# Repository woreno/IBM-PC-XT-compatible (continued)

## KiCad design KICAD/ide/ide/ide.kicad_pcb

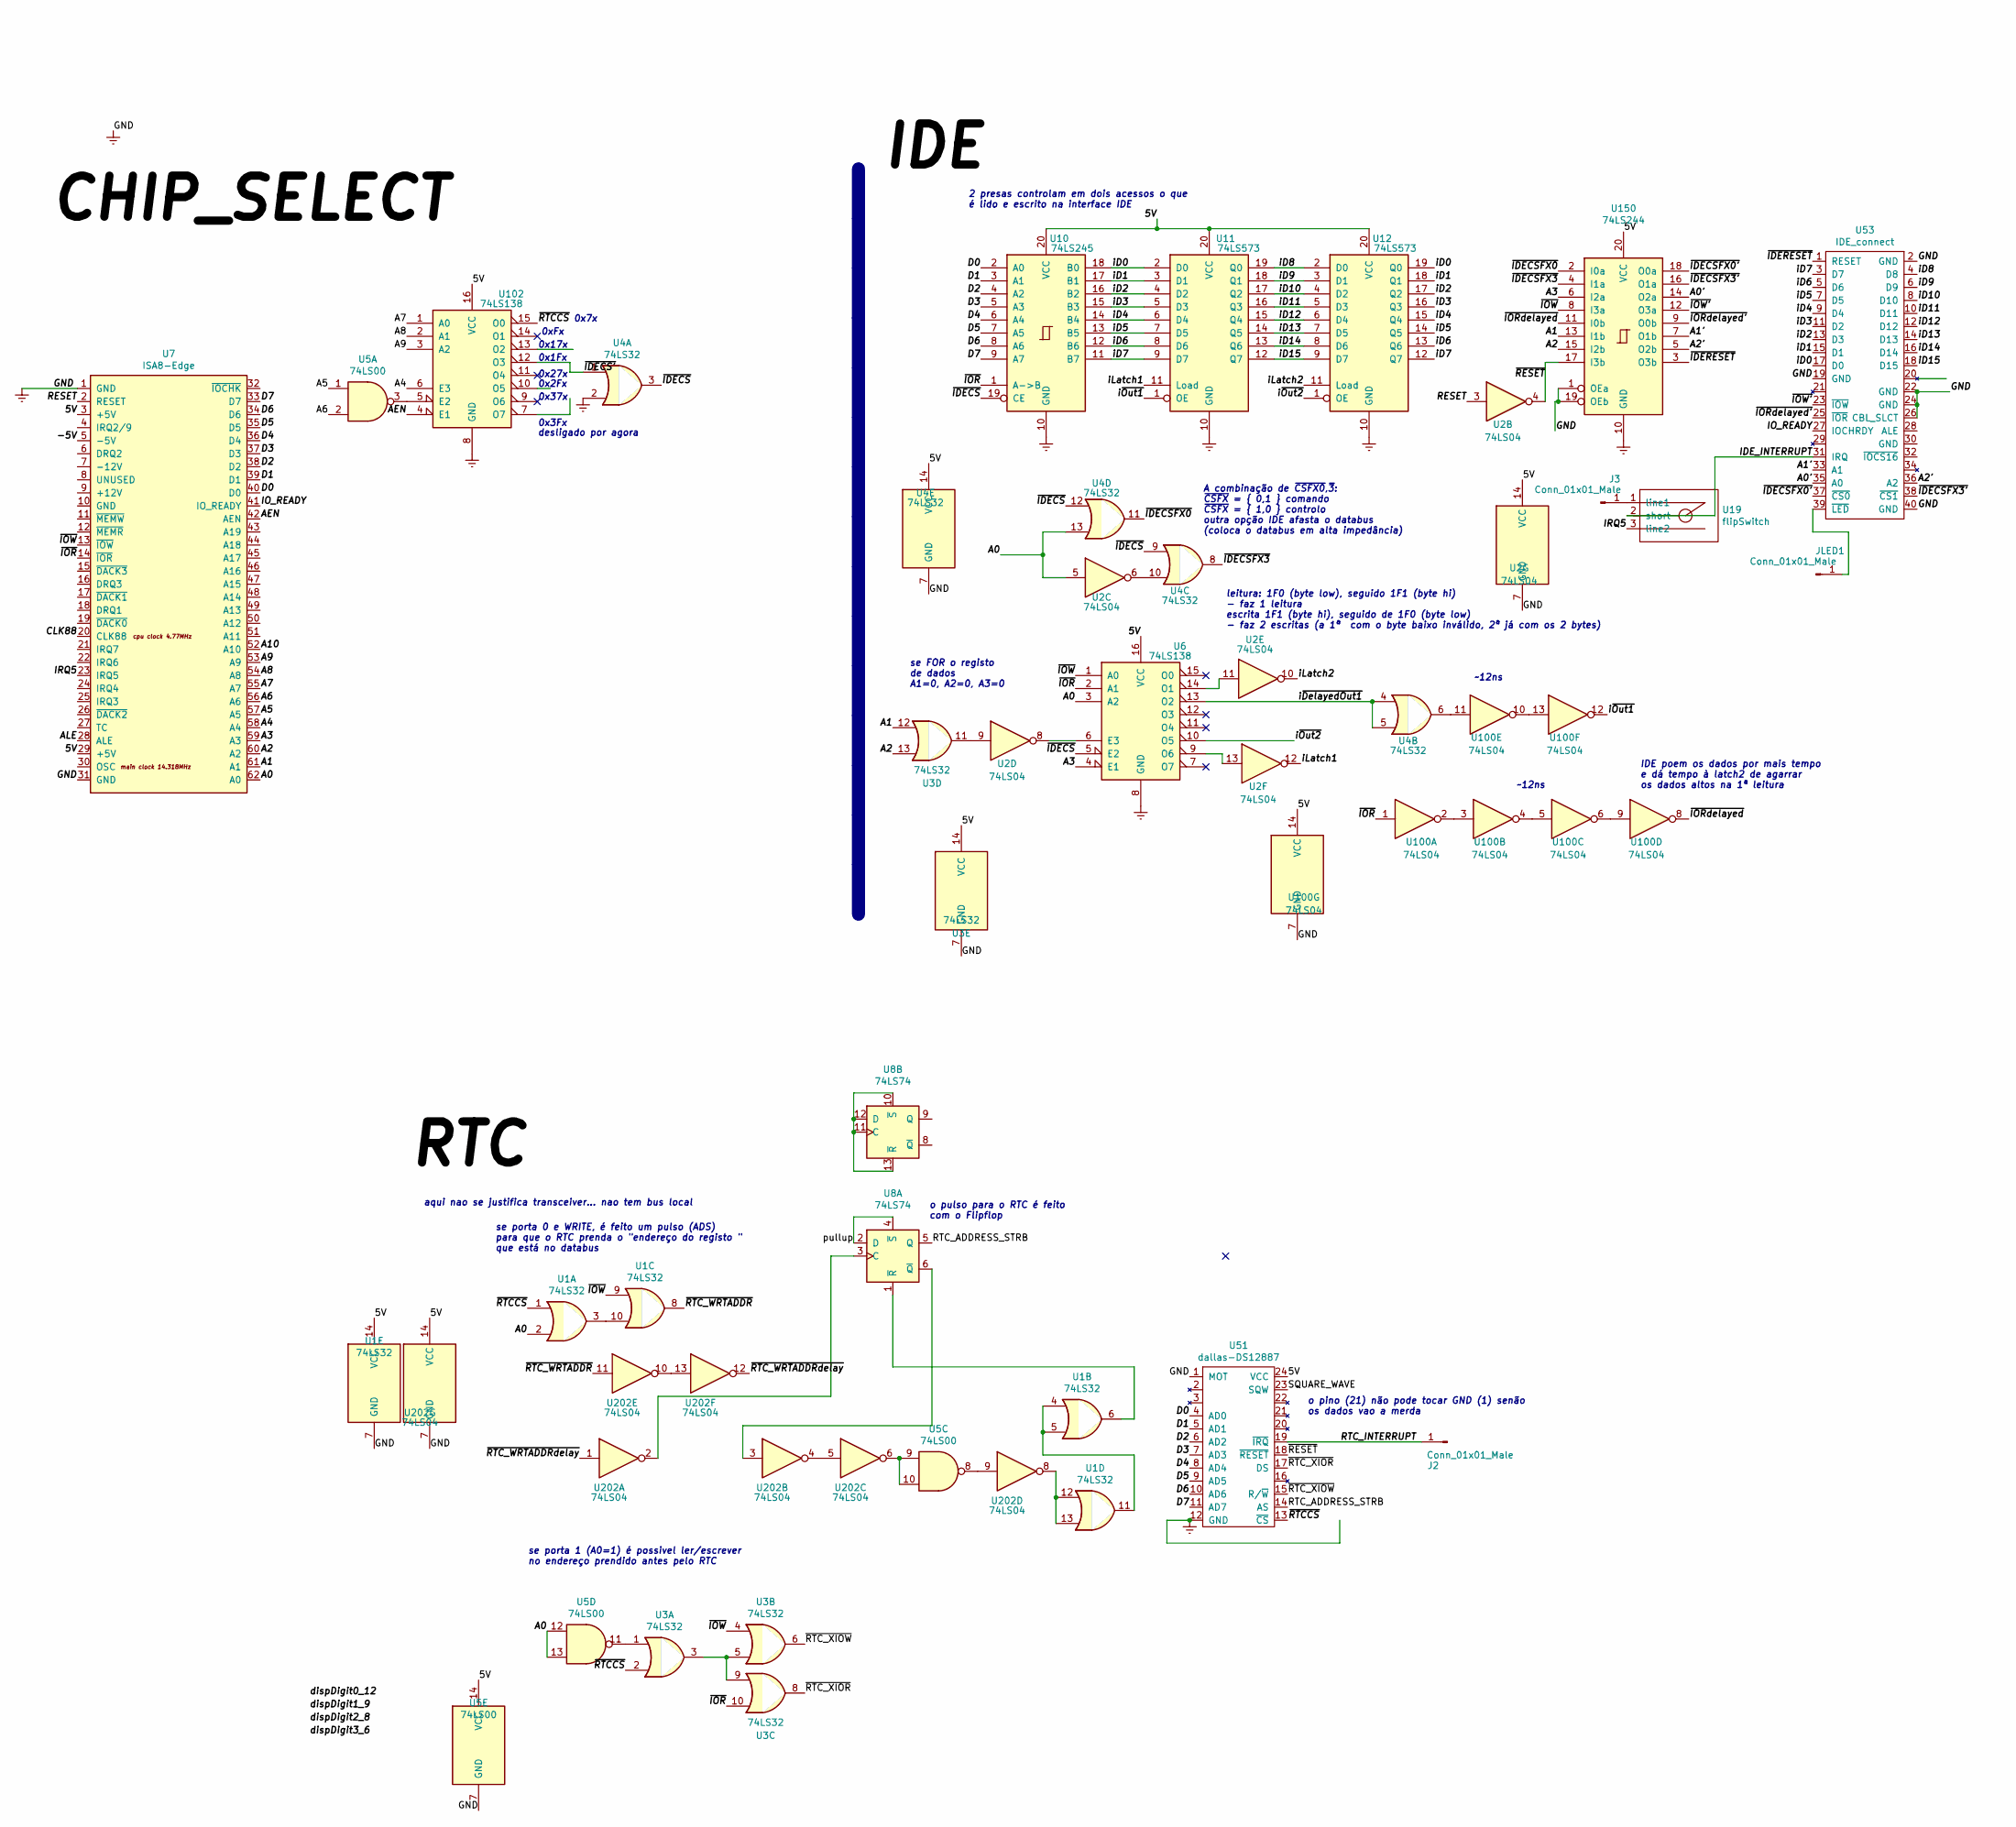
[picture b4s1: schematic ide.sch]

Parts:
J2, J3: Conn_01x01_Male; Conector1x1_Oval
JLED1: Conn_01x01_Male; Conector1x1_Oval
U1, U3, U4: 74LS32; standard_DIP_14OvalPins
U2, U100, U202: 74LS04; standard_DIP_14OvalPins
U5: 74LS00; standard_DIP_14OvalPins
U6, U102: 74LS138; standard_DIP_16OvalPins
U7: ISA8-Edge; ISA_8bit_edge
U8: 74LS74; standard_DIP_14OvalPins
U10: 74LS245; standard_DIP_20pins_thin_body
U11, U12: 74LS573; standard_DIP_20pins_thin_body
U19: flipSwitch; mini_flipswitch2.54
U51: dallas-DS12887; standard_DIP_24pins_thin_doubleBody
U53: IDE_connect; Conector2x20_Oval_alternado
U150: 74LS244; standard_DIP_20pins_thin_body

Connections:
/5V: U1.14 (VCC), U2.14 (VCC), U3.14 (VCC), U4.14 (VCC), U5.14 (VCC), U6.16 (VCC), U7.3 (+5V), U7.29 (+5V), U10.20 (VCC), U11.20 (VCC), U12.20 (VCC), U51.24 (VCC), U100.14 (VCC), U102.16 (VCC), U150.20 (VCC), U202.14 (VCC)
/-5V: U7.5 (-5V)
/A0: U1.2, U2.5, U4.13, U5.12, U5.13, U6.3 (A2), U7.62 (A0)
/A0': U53.35 (A0), U150.14 (O2a)
/A1: U3.12, U7.61 (A1), U150.13 (I1b)
/A1': U53.33 (A1), U150.7 (O1b)
/A2: U3.13, U7.60 (A2), U150.15 (I2b)
/A2': U53.36 (A2), U150.5 (O2b)
/A3: U6.4 (E1), U7.59 (A3), U150.6 (I2a)
/A4: U7.58 (A4), U102.6 (E3)
/A5: U5.1, U7.57 (A5)
/A6: U5.2, U7.56 (A6)
/A7: U7.55 (A7), U102.1 (A0)
/A8: U7.54 (A8), U102.2 (A1)
/A9: U7.53 (A9), U102.3 (A2)
/A10: U7.52 (A10)
/AEN: U7.42 (AEN), U102.4 (E1)
/ALE: U7.28 (ALE)
/CLK88: U7.20 (CLK88)
/D0: U7.40 (D0), U10.2 (A0), U51.4 (AD0)
/D1: U7.39 (D1), U10.3 (A1), U51.5 (AD1)
/D2: U7.38 (D2), U10.4 (A2), U51.6 (AD2)
/D3: U7.37 (D3), U10.5 (A3), U51.7 (AD3)
/D4: U7.36 (D4), U10.6 (A4), U51.8 (AD4)
/D5: U7.35 (D5), U10.7 (A5), U51.9 (AD5)
/D6: U7.34 (D6), U10.8 (A6), U51.10 (AD6)
/D7: U7.33 (D7), U10.9 (A7), U51.11 (AD7)
/IDE_INTERRUPT: U19.2 (short), U53.31 (IRQ)
/IO_READY: U7.41 (IO_READY), U53.27 (IOCHRDY)
/IRQ5: U7.23 (IRQ5), U19.3 (line2)
/RESET: U2.3, U7.2 (RESET)
/RTC_ADDRESS_STRB: U8.5 (Q), U51.14 (AS)
/RTC_INTERRUPT: J2.1, U51.19 (~IRQ)
/SQUARE_WAVE: U51.23 (SQW)
/iD0: U10.18 (B0), U11.2 (D0), U12.19 (Q0), U53.17 (D0)
/iD1: U10.17 (B1), U11.3 (D1), U12.18 (Q1), U53.15 (D1)
/iD2: U10.16 (B2), U11.4 (D2), U12.17 (Q2), U53.13 (D3)
/iD3: U10.15 (B3), U11.5 (D3), U12.16 (Q3), U53.11 (D2)
/iD4: U10.14 (B4), U11.6 (D4), U12.15 (Q4), U53.9 (D4)
/iD5: U10.13 (B5), U11.7 (D5), U12.14 (Q5), U53.7 (D5)
/iD6: U10.12 (B6), U11.8 (D6), U12.13 (Q6), U53.5 (D6)
/iD7: U10.11 (B7), U11.9 (D7), U12.12 (Q7), U53.3 (D7)
/iD8: U11.19 (Q0), U12.2 (D0), U53.4 (D8)
/iD9: U11.18 (Q1), U12.3 (D1), U53.6 (D9)
/iD10: U11.17 (Q2), U12.4 (D2), U53.8 (D10)
/iD11: U11.16 (Q3), U12.5 (D3), U53.10 (D11)
/iD12: U11.15 (Q4), U12.6 (D4), U53.12 (D12)
/iD13: U11.14 (Q5), U12.7 (D5), U53.14 (D13)
/iD14: U11.13 (Q6), U12.8 (D6), U53.16 (D14)
/iD15: U11.12 (Q7), U12.9 (D7), U53.18 (D15)
/iLatch1: U2.12, U11.11 (Load)
/iLatch2: U2.10, U12.11 (Load)
/i~DelayedOut1: U4.4, U4.5, U6.13 (O2)
/i~Out1: U11.1 (OE), U100.12
/i~Out2: U6.10 (O5), U12.1 (OE)
/pullup: U8.2 (D), U8.4 (~S)
/~IDECS: U4.3, U4.9, U4.12, U6.5 (E2), U10.19 (CE)
/~IDECS': U4.1, U102.12 (O3)
/~IDECSFX0: U4.11, U150.2 (I0a)
/~IDECSFX0': U53.37 (~CS0), U150.18 (O0a)
/~IDECSFX3: U4.8, U150.4 (I1a)
/~IDECSFX3': U53.38 (~CS1), U150.16 (O1a)
/~IDERESET: U53.1 (RESET), U150.3 (O3b)
/~IOR: U3.10, U6.2 (A1), U7.14 (~IOR), U10.1 (A->B), U100.1
/~IORdelayed: U100.8, U150.11 (I0b)
/~IORdelayed': U53.25 (~IOR), U150.9 (O0b)
/~IOW: U1.9, U3.4, U6.1 (A0), U7.13 (~IOW), U150.8 (I3a)
/~IOW': U53.23 (~IOW), U150.12 (O3a)
/~RESET: U2.4, U51.18 (~RESET), U150.17 (I3b)
/~RTCCS: U1.1, U3.2, U51.13 (~CS), U102.15 (O0)
/~RTC_WRTADDR: U1.8, U202.11
/~RTC_WRTADDRdelay: U202.1, U202.12
/~RTC_XIOR: U3.8, U51.17 (DS)
/~RTC_XIOW: U3.6, U51.15 (R/~W)
Earth: U1.7 (GND), U2.7 (GND), U3.7 (GND), U4.2, U4.7 (GND), U5.7 (GND), U6.8 (GND), U7.1 (GND), U7.31 (GND), U10.10 (GND), U11.10 (GND), U12.10 (GND), U51.1 (MOT), U51.12 (GND), U53.2 (GND), U53.19 (GND), U53.22 (GND), U53.24 (GND), U53.26 (CBL_SLCT), U53.40 (GND), U100.7 (GND), U102.8 (GND), U150.1 (OEa), U150.10 (GND), U150.19 (OEb), U202.7 (GND)
unnamed: J3.1, U19.1 (line1)
unnamed: JLED1.1, U53.39 (~LED)
unnamed: U1.6, U8.1 (~R)
unnamed: U1.3, U1.10
unnamed: U1.4, U1.5, U1.11
unnamed: U1.12, U1.13, U202.8
unnamed: U2.6, U4.10
unnamed: U2.8, U6.6 (E3)
unnamed: U2.9, U3.11
unnamed: U2.11, U6.14 (O1)
unnamed: U2.13, U6.9 (O6)
unnamed: U3.1, U5.11
unnamed: U3.3, U3.5, U3.9
unnamed: U8.10 (~S), U8.11 (C), U8.12 (D), U8.13 (~R)
unnamed: U100.2, U100.3
unnamed: U100.4, U100.5
unnamed: U100.6, U100.9
unnamed: U100.10, U100.13
unnamed: U4.6, U100.11
unnamed: U5.3, U102.5 (E2)
unnamed: U8.3 (C), U202.2
unnamed: U8.6 (~Q), U202.3
unnamed: U202.4, U202.5
unnamed: U5.9, U5.10, U202.6
unnamed: U5.8, U202.9
unnamed: U202.10, U202.13

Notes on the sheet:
o pino (21) não pode tocar GND (1) senão os dados vao a merda
~~12ns
A combinação de ~CSFX0~,~3~: ~CSFX~ = { 0,1 } comando ~CSFX~ = { 1,0 } controlo outra opção IDE afasta o databus (coloca o databus em alta impedância)
2 presas controlam em dois acessos o que é lido e escrito na interface IDE
_______________
aqui nao se justifica transceiver... nao tem bus local
se porta 1 (A0=1) é possivel ler/escrever no endereço prendido antes pelo RTC
0x3Fx
0x1Fx
0x7x
0x17x
0xFx
0x27x
0x2Fx
0x37x
desligado por agora
se FOR o registo de dados A1=0, A2=0, A3=0
leitura: 1F0 (byte low), seguido 1F1 (byte hi) - faz 1 leitura escrita 1F1 (byte hi), seguido de 1F0 (byte low) - faz 2 escritas (a 1ª com o byte baixo inválido, 2ª já com os 2 bytes)
IDE poem os dados por mais tempo e dá tempo à latch2 de agarrar os dados altos na 1ª leitura
se porta 0 e WRITE, é feito um pulso (ADS) para que o RTC prenda o "endereço do registo " que está no databus
o pulso para o RTC é feito com o Flipflop

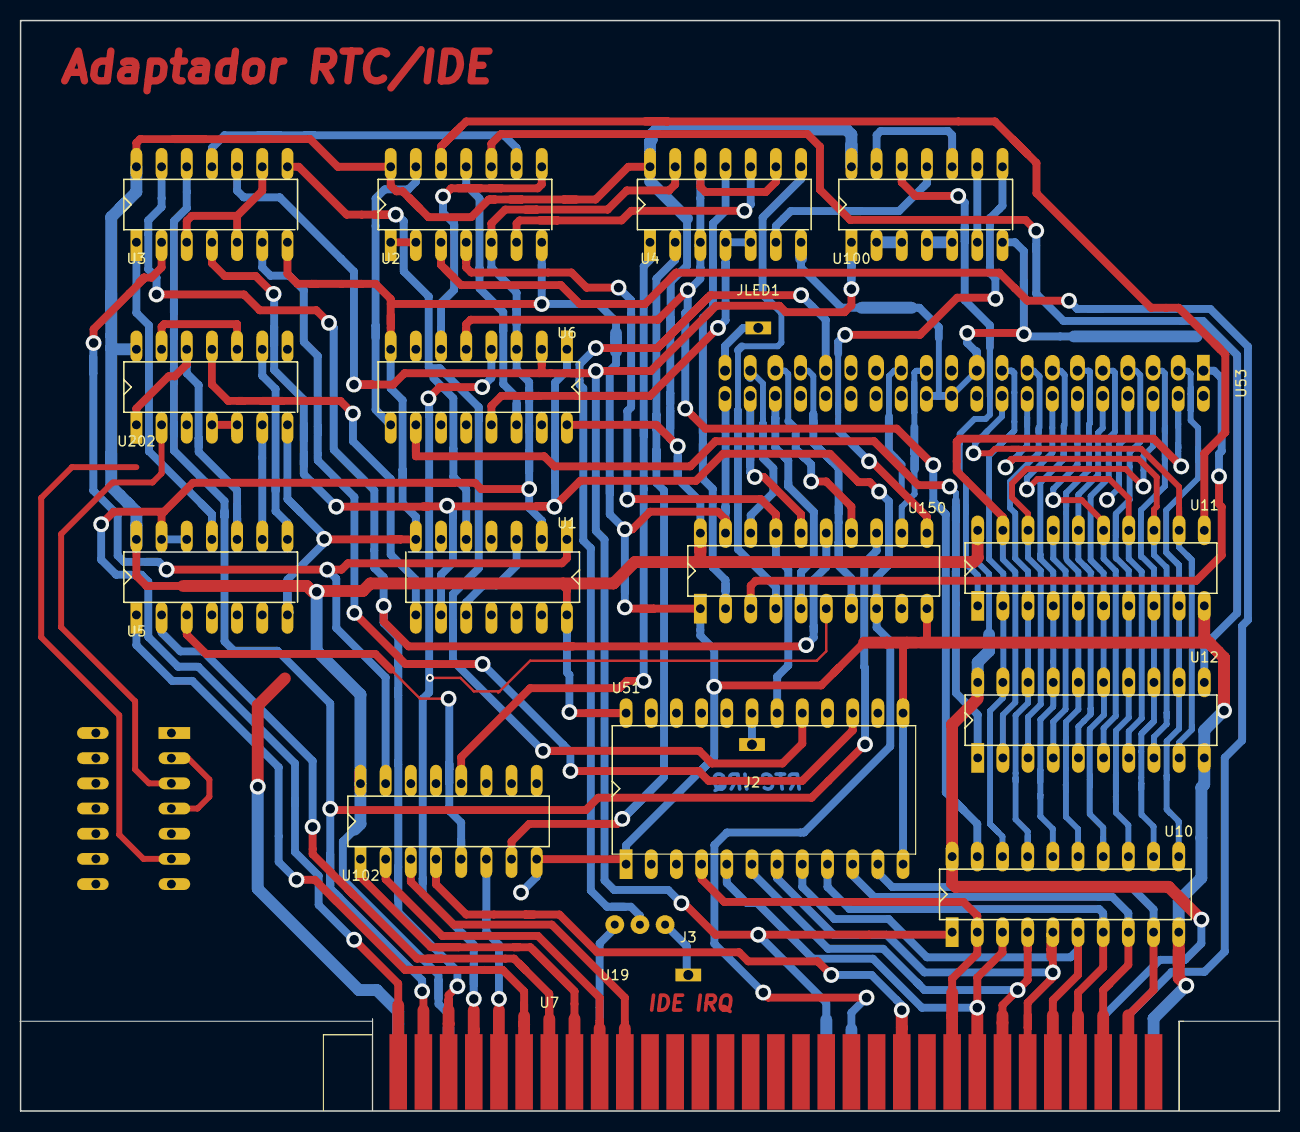
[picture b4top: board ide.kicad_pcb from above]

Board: 2 copper layers, 127.0 x 110.0 mm, 21 parts (1 on the bottom side), 96 nets.

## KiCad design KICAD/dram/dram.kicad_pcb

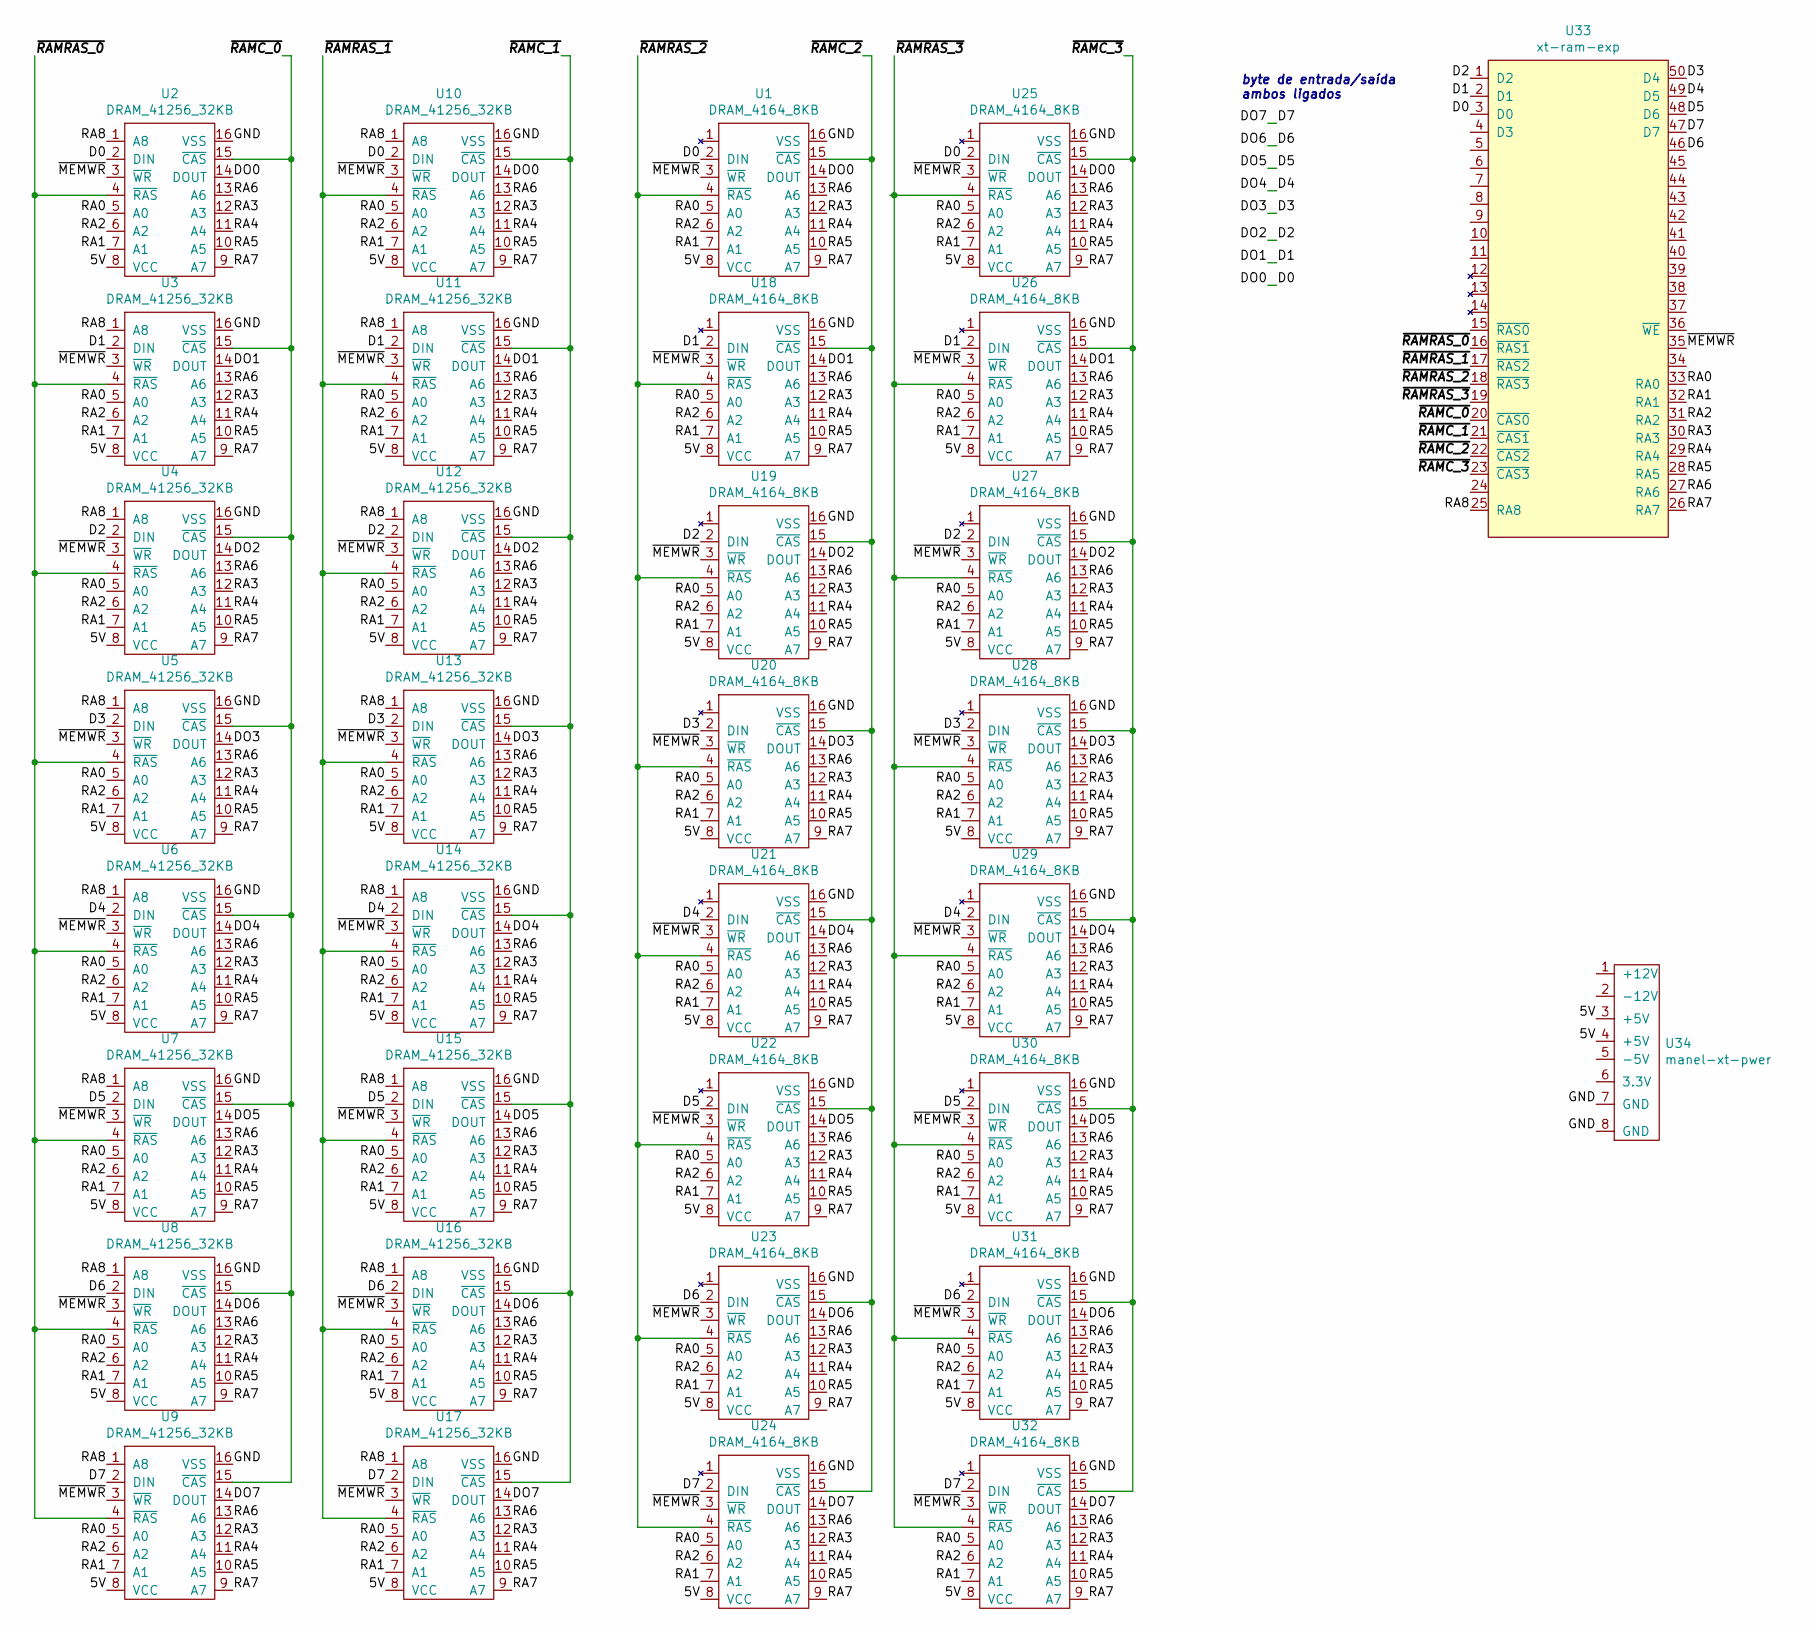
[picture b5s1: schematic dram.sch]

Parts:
U1, U18, U19, U20, U21, U22, U23, U24, U25, U26, U27, U28, U29, U30, U31, U32: DRAM_4164_8KB; standard_DIP_16OvalPins
U2, U3, U4, U5, U6, U7, U8, U9, U10, U11, U12, U13, U14, U15, U16, U17: DRAM_41256_32KB; standard_DIP_16OvalPins
U33: xt-ram-exp; xt-ram-edge
U34: manel-xt-pwer; manel-xt-power

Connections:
/5V: U1.8 (VCC), U2.8 (VCC), U3.8 (VCC), U4.8 (VCC), U5.8 (VCC), U6.8 (VCC), U7.8 (VCC), U8.8 (VCC), U9.8 (VCC), U10.8 (VCC), U11.8 (VCC), U12.8 (VCC), U13.8 (VCC), U14.8 (VCC), U15.8 (VCC), U16.8 (VCC), U17.8 (VCC), U18.8 (VCC), U19.8 (VCC), U20.8 (VCC), U21.8 (VCC), U22.8 (VCC), U23.8 (VCC), U24.8 (VCC), U25.8 (VCC), U26.8 (VCC), U27.8 (VCC), U28.8 (VCC), U29.8 (VCC), U30.8 (VCC), U31.8 (VCC), U32.8 (VCC), U34.3 (+5V), U34.4 (+5V)
/D0: U1.2 (DIN), U1.14 (DOUT), U2.2 (DIN), U2.14 (DOUT), U10.2 (DIN), U10.14 (DOUT), U25.2 (DIN), U25.14 (DOUT), U33.3 (D0)
/D1: U3.2 (DIN), U3.14 (DOUT), U11.2 (DIN), U11.14 (DOUT), U18.2 (DIN), U18.14 (DOUT), U26.2 (DIN), U26.14 (DOUT), U33.2 (D1)
/D2: U4.2 (DIN), U4.14 (DOUT), U12.2 (DIN), U12.14 (DOUT), U19.2 (DIN), U19.14 (DOUT), U27.2 (DIN), U27.14 (DOUT), U33.1 (D2)
/D3: U5.2 (DIN), U5.14 (DOUT), U13.2 (DIN), U13.14 (DOUT), U20.2 (DIN), U20.14 (DOUT), U28.2 (DIN), U28.14 (DOUT), U33.50 (D4)
/D4: U6.2 (DIN), U6.14 (DOUT), U14.2 (DIN), U14.14 (DOUT), U21.2 (DIN), U21.14 (DOUT), U29.2 (DIN), U29.14 (DOUT), U33.49 (D5)
/D5: U7.2 (DIN), U7.14 (DOUT), U15.2 (DIN), U15.14 (DOUT), U22.2 (DIN), U22.14 (DOUT), U30.2 (DIN), U30.14 (DOUT), U33.48 (D6)
/D6: U8.2 (DIN), U8.14 (DOUT), U16.2 (DIN), U16.14 (DOUT), U23.2 (DIN), U23.14 (DOUT), U31.2 (DIN), U31.14 (DOUT), U33.46
/D7: U9.2 (DIN), U9.14 (DOUT), U17.2 (DIN), U17.14 (DOUT), U24.2 (DIN), U24.14 (DOUT), U32.2 (DIN), U32.14 (DOUT), U33.47 (D7)
/GND: U1.16 (VSS), U2.16 (VSS), U3.16 (VSS), U4.16 (VSS), U5.16 (VSS), U6.16 (VSS), U7.16 (VSS), U8.16 (VSS), U9.16 (VSS), U10.16 (VSS), U11.16 (VSS), U12.16 (VSS), U13.16 (VSS), U14.16 (VSS), U15.16 (VSS), U16.16 (VSS), U17.16 (VSS), U18.16 (VSS), U19.16 (VSS), U20.16 (VSS), U21.16 (VSS), U22.16 (VSS), U23.16 (VSS), U24.16 (VSS), U25.16 (VSS), U26.16 (VSS), U27.16 (VSS), U28.16 (VSS), U29.16 (VSS), U30.16 (VSS), U31.16 (VSS), U32.16 (VSS), U34.7 (GND), U34.8 (GND)
/RA0: U1.5 (A0), U2.5 (A0), U3.5 (A0), U4.5 (A0), U5.5 (A0), U6.5 (A0), U7.5 (A0), U8.5 (A0), U9.5 (A0), U10.5 (A0), U11.5 (A0), U12.5 (A0), U13.5 (A0), U14.5 (A0), U15.5 (A0), U16.5 (A0), U17.5 (A0), U18.5 (A0), U19.5 (A0), U20.5 (A0), U21.5 (A0), U22.5 (A0), U23.5 (A0), U24.5 (A0), U25.5 (A0), U26.5 (A0), U27.5 (A0), U28.5 (A0), U29.5 (A0), U30.5 (A0), U31.5 (A0), U32.5 (A0), U33.33 (RA0)
/RA1: U1.7 (A1), U2.7 (A1), U3.7 (A1), U4.7 (A1), U5.7 (A1), U6.7 (A1), U7.7 (A1), U8.7 (A1), U9.7 (A1), U10.7 (A1), U11.7 (A1), U12.7 (A1), U13.7 (A1), U14.7 (A1), U15.7 (A1), U16.7 (A1), U17.7 (A1), U18.7 (A1), U19.7 (A1), U20.7 (A1), U21.7 (A1), U22.7 (A1), U23.7 (A1), U24.7 (A1), U25.7 (A1), U26.7 (A1), U27.7 (A1), U28.7 (A1), U29.7 (A1), U30.7 (A1), U31.7 (A1), U32.7 (A1), U33.32 (RA1)
/RA2: U1.6 (A2), U2.6 (A2), U3.6 (A2), U4.6 (A2), U5.6 (A2), U6.6 (A2), U7.6 (A2), U8.6 (A2), U9.6 (A2), U10.6 (A2), U11.6 (A2), U12.6 (A2), U13.6 (A2), U14.6 (A2), U15.6 (A2), U16.6 (A2), U17.6 (A2), U18.6 (A2), U19.6 (A2), U20.6 (A2), U21.6 (A2), U22.6 (A2), U23.6 (A2), U24.6 (A2), U25.6 (A2), U26.6 (A2), U27.6 (A2), U28.6 (A2), U29.6 (A2), U30.6 (A2), U31.6 (A2), U32.6 (A2), U33.31 (RA2)
/RA3: U1.12 (A3), U2.12 (A3), U3.12 (A3), U4.12 (A3), U5.12 (A3), U6.12 (A3), U7.12 (A3), U8.12 (A3), U9.12 (A3), U10.12 (A3), U11.12 (A3), U12.12 (A3), U13.12 (A3), U14.12 (A3), U15.12 (A3), U16.12 (A3), U17.12 (A3), U18.12 (A3), U19.12 (A3), U20.12 (A3), U21.12 (A3), U22.12 (A3), U23.12 (A3), U24.12 (A3), U25.12 (A3), U26.12 (A3), U27.12 (A3), U28.12 (A3), U29.12 (A3), U30.12 (A3), U31.12 (A3), U32.12 (A3), U33.30 (RA3)
/RA4: U1.11 (A4), U2.11 (A4), U3.11 (A4), U4.11 (A4), U5.11 (A4), U6.11 (A4), U7.11 (A4), U8.11 (A4), U9.11 (A4), U10.11 (A4), U11.11 (A4), U12.11 (A4), U13.11 (A4), U14.11 (A4), U15.11 (A4), U16.11 (A4), U17.11 (A4), U18.11 (A4), U19.11 (A4), U20.11 (A4), U21.11 (A4), U22.11 (A4), U23.11 (A4), U24.11 (A4), U25.11 (A4), U26.11 (A4), U27.11 (A4), U28.11 (A4), U29.11 (A4), U30.11 (A4), U31.11 (A4), U32.11 (A4), U33.29 (RA4)
/RA5: U1.10 (A5), U2.10 (A5), U3.10 (A5), U4.10 (A5), U5.10 (A5), U6.10 (A5), U7.10 (A5), U8.10 (A5), U9.10 (A5), U10.10 (A5), U11.10 (A5), U12.10 (A5), U13.10 (A5), U14.10 (A5), U15.10 (A5), U16.10 (A5), U17.10 (A5), U18.10 (A5), U19.10 (A5), U20.10 (A5), U21.10 (A5), U22.10 (A5), U23.10 (A5), U24.10 (A5), U25.10 (A5), U26.10 (A5), U27.10 (A5), U28.10 (A5), U29.10 (A5), U30.10 (A5), U31.10 (A5), U32.10 (A5), U33.28 (RA5)
/RA6: U1.13 (A6), U2.13 (A6), U3.13 (A6), U4.13 (A6), U5.13 (A6), U6.13 (A6), U7.13 (A6), U8.13 (A6), U9.13 (A6), U10.13 (A6), U11.13 (A6), U12.13 (A6), U13.13 (A6), U14.13 (A6), U15.13 (A6), U16.13 (A6), U17.13 (A6), U18.13 (A6), U19.13 (A6), U20.13 (A6), U21.13 (A6), U22.13 (A6), U23.13 (A6), U24.13 (A6), U25.13 (A6), U26.13 (A6), U27.13 (A6), U28.13 (A6), U29.13 (A6), U30.13 (A6), U31.13 (A6), U32.13 (A6), U33.27 (RA6)
/RA7: U1.9 (A7), U2.9 (A7), U3.9 (A7), U4.9 (A7), U5.9 (A7), U6.9 (A7), U7.9 (A7), U8.9 (A7), U9.9 (A7), U10.9 (A7), U11.9 (A7), U12.9 (A7), U13.9 (A7), U14.9 (A7), U15.9 (A7), U16.9 (A7), U17.9 (A7), U18.9 (A7), U19.9 (A7), U20.9 (A7), U21.9 (A7), U22.9 (A7), U23.9 (A7), U24.9 (A7), U25.9 (A7), U26.9 (A7), U27.9 (A7), U28.9 (A7), U29.9 (A7), U30.9 (A7), U31.9 (A7), U32.9 (A7), U33.26 (RA7)
/RA8: U2.1 (A8), U3.1 (A8), U4.1 (A8), U5.1 (A8), U6.1 (A8), U7.1 (A8), U8.1 (A8), U9.1 (A8), U10.1 (A8), U11.1 (A8), U12.1 (A8), U13.1 (A8), U14.1 (A8), U15.1 (A8), U16.1 (A8), U17.1 (A8), U33.25 (RA8)
/~MEMWR: U1.3 (~WR), U2.3 (~WR), U3.3 (~WR), U4.3 (~WR), U5.3 (~WR), U6.3 (~WR), U7.3 (~WR), U8.3 (~WR), U9.3 (~WR), U10.3 (~WR), U11.3 (~WR), U12.3 (~WR), U13.3 (~WR), U14.3 (~WR), U15.3 (~WR), U16.3 (~WR), U17.3 (~WR), U18.3 (~WR), U19.3 (~WR), U20.3 (~WR), U21.3 (~WR), U22.3 (~WR), U23.3 (~WR), U24.3 (~WR), U25.3 (~WR), U26.3 (~WR), U27.3 (~WR), U28.3 (~WR), U29.3 (~WR), U30.3 (~WR), U31.3 (~WR), U32.3 (~WR), U33.35
/~RAMC_0: U2.15 (~CAS), U3.15 (~CAS), U4.15 (~CAS), U5.15 (~CAS), U6.15 (~CAS), U7.15 (~CAS), U8.15 (~CAS), U9.15 (~CAS), U33.20 (~CAS0)
/~RAMC_1: U10.15 (~CAS), U11.15 (~CAS), U12.15 (~CAS), U13.15 (~CAS), U14.15 (~CAS), U15.15 (~CAS), U16.15 (~CAS), U17.15 (~CAS), U33.21 (~CAS1)
/~RAMC_2: U1.15 (~CAS), U18.15 (~CAS), U19.15 (~CAS), U20.15 (~CAS), U21.15 (~CAS), U22.15 (~CAS), U23.15 (~CAS), U24.15 (~CAS), U33.22 (~CAS2)
/~RAMC_3: U25.15 (~CAS), U26.15 (~CAS), U27.15 (~CAS), U28.15 (~CAS), U29.15 (~CAS), U30.15 (~CAS), U31.15 (~CAS), U32.15 (~CAS), U33.23 (~CAS3)
/~RAMRAS_0: U2.4 (~RAS), U3.4 (~RAS), U4.4 (~RAS), U5.4 (~RAS), U6.4 (~RAS), U7.4 (~RAS), U8.4 (~RAS), U9.4 (~RAS), U33.16 (~RAS1)
/~RAMRAS_1: U10.4 (~RAS), U11.4 (~RAS), U12.4 (~RAS), U13.4 (~RAS), U14.4 (~RAS), U15.4 (~RAS), U16.4 (~RAS), U17.4 (~RAS), U33.17 (~RAS2)
/~RAMRAS_2: U1.4 (~RAS), U18.4 (~RAS), U19.4 (~RAS), U20.4 (~RAS), U21.4 (~RAS), U22.4 (~RAS), U23.4 (~RAS), U24.4 (~RAS), U33.18 (~RAS3)
/~RAMRAS_3: U25.4 (~RAS), U26.4 (~RAS), U27.4 (~RAS), U28.4 (~RAS), U29.4 (~RAS), U30.4 (~RAS), U31.4 (~RAS), U32.4 (~RAS), U33.19

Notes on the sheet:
byte de entrada/saída ambos ligados

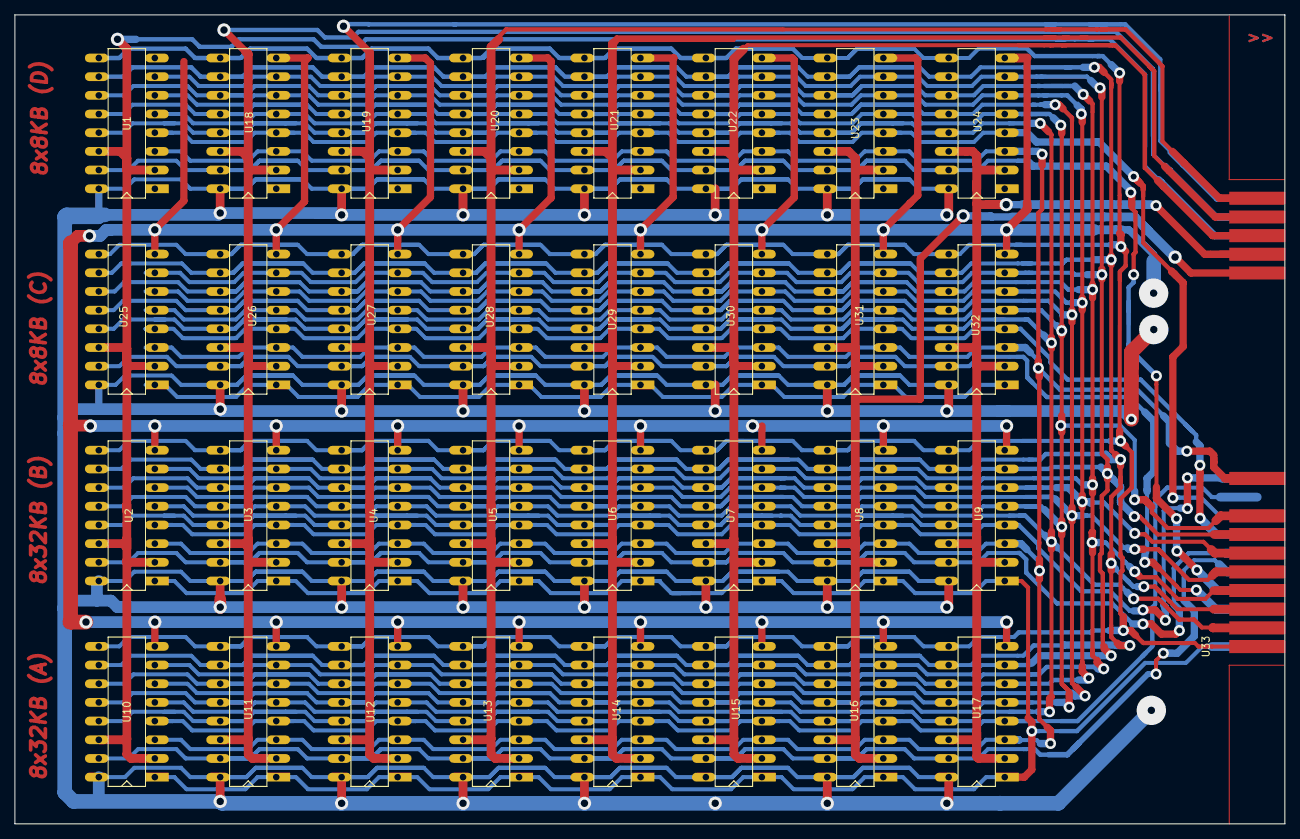
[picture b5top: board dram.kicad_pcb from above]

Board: 2 copper layers, 172.7 x 110.0 mm, 33 parts (0 on the bottom side), 28 nets.
